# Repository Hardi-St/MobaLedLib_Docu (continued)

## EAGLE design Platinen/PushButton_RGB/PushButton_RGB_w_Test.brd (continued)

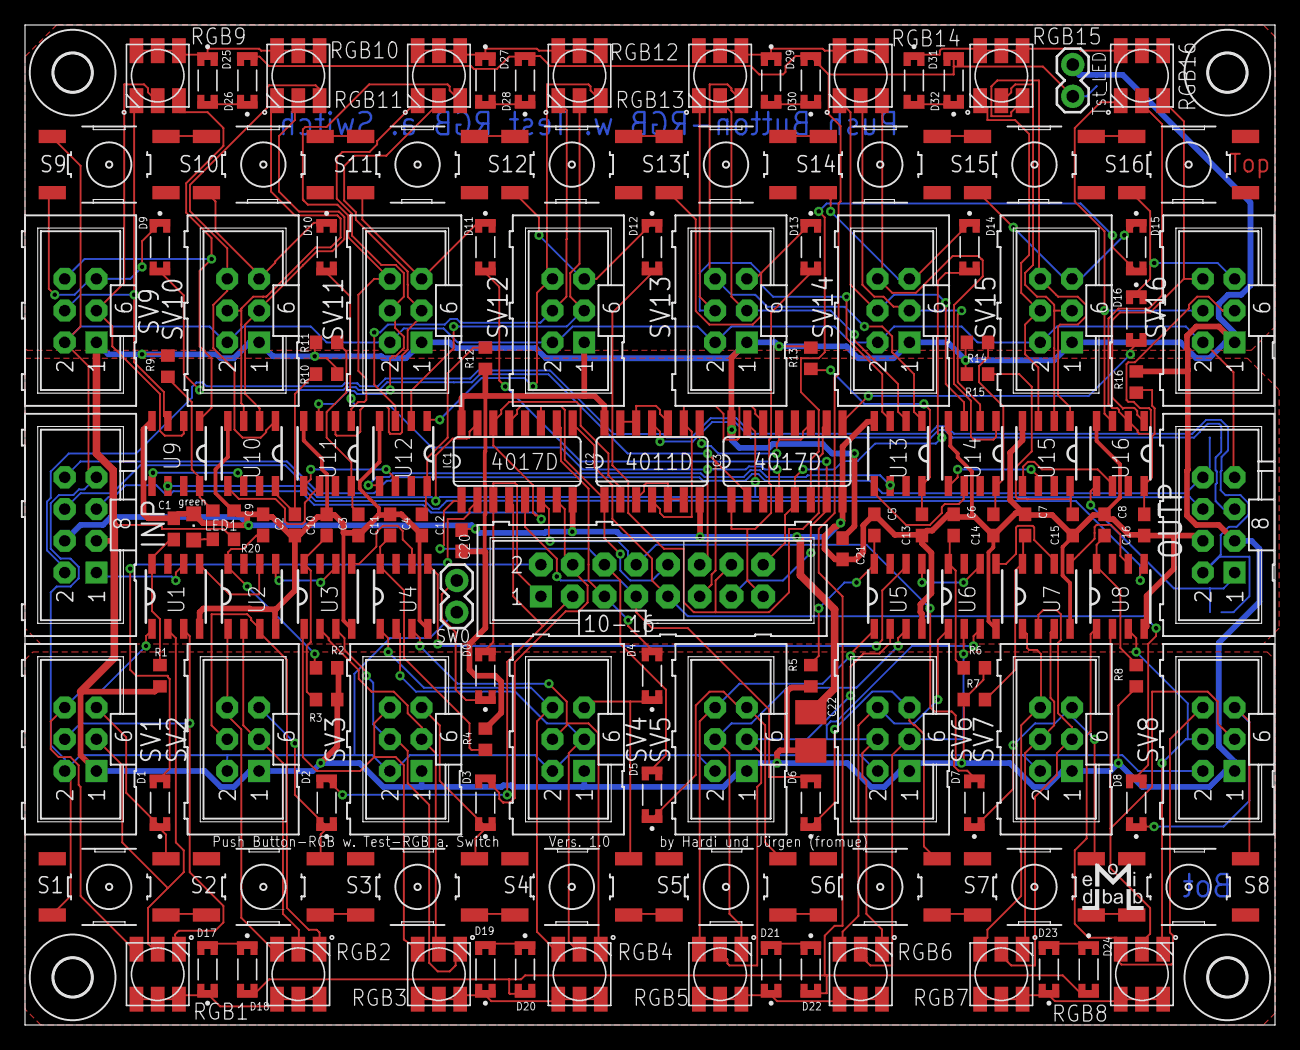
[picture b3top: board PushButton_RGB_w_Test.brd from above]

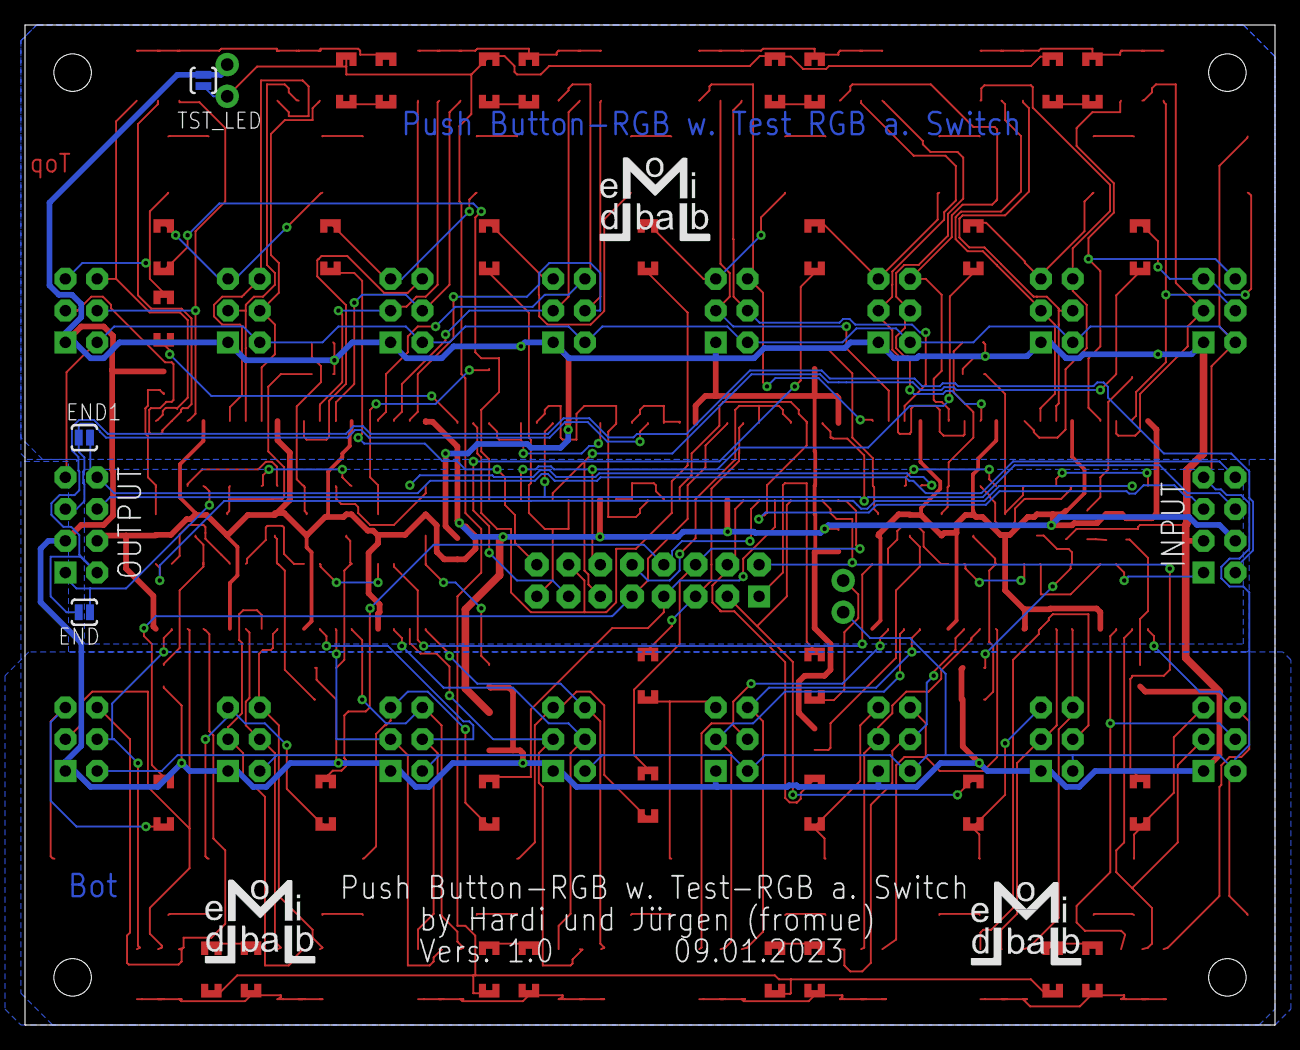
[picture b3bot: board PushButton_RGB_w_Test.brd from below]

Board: 2 copper layers, 100.0 x 80.0 mm, 149 parts (3 on the bottom side), 160 nets.

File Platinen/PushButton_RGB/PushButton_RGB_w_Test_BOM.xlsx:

Comment | Designator | Footprint | JLCPCB Part #（optional）
E OMRON SWITCH | S1, S2, S3, S4, S5, S6, S7, S8, S9, S10, S11, S12, S13, S14, S15, S16 | B3F-10XX_SMD | C83916
E WS2811 | U1, U2, U3, U4, U5, U6, U7, U8, U9, U10, U11, U12, U13, U14, U15, U16 | SOP8 | C114581
B 100nF | C1, C2, C3, C4, C5, C6, C7, C8, C9, C10, C11, C12, C13, C14, C15, C16, C20, C21 | C0603 | C14663
B 100uF CA45A-B-6.3V-100uF-K | C22 | B/3528-21R | C16133
E 4011 Quad 2-input NAND | IC2 | SO14 | C194334
E 4017 Counter | IC1, IC3 | SO16 | C356694
B 470 Ohm | R1, R2, R3, R4, R5, R6, R7, R8, R9, R10, R11, R12, R13, R14, R15, R16, R20 | R0603 | C23179
B LL4148 | D0, D1, D2, D3, D4, D5, D6, D7, D8, D9, D10, D11, D12, D13, D14, D15, D16, D17,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 | DIO_LL4148 | C9808
E 5050 RGB LED TC5050RGBF08-3CJH-AF53A | RGB1, RGB2, RGB3, RGB4, RGB5, RGB6, RGB7, RGB8, RGB9, RGB10, RGB11, RGB12, RGB1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 | RGBLED5050 | C784540

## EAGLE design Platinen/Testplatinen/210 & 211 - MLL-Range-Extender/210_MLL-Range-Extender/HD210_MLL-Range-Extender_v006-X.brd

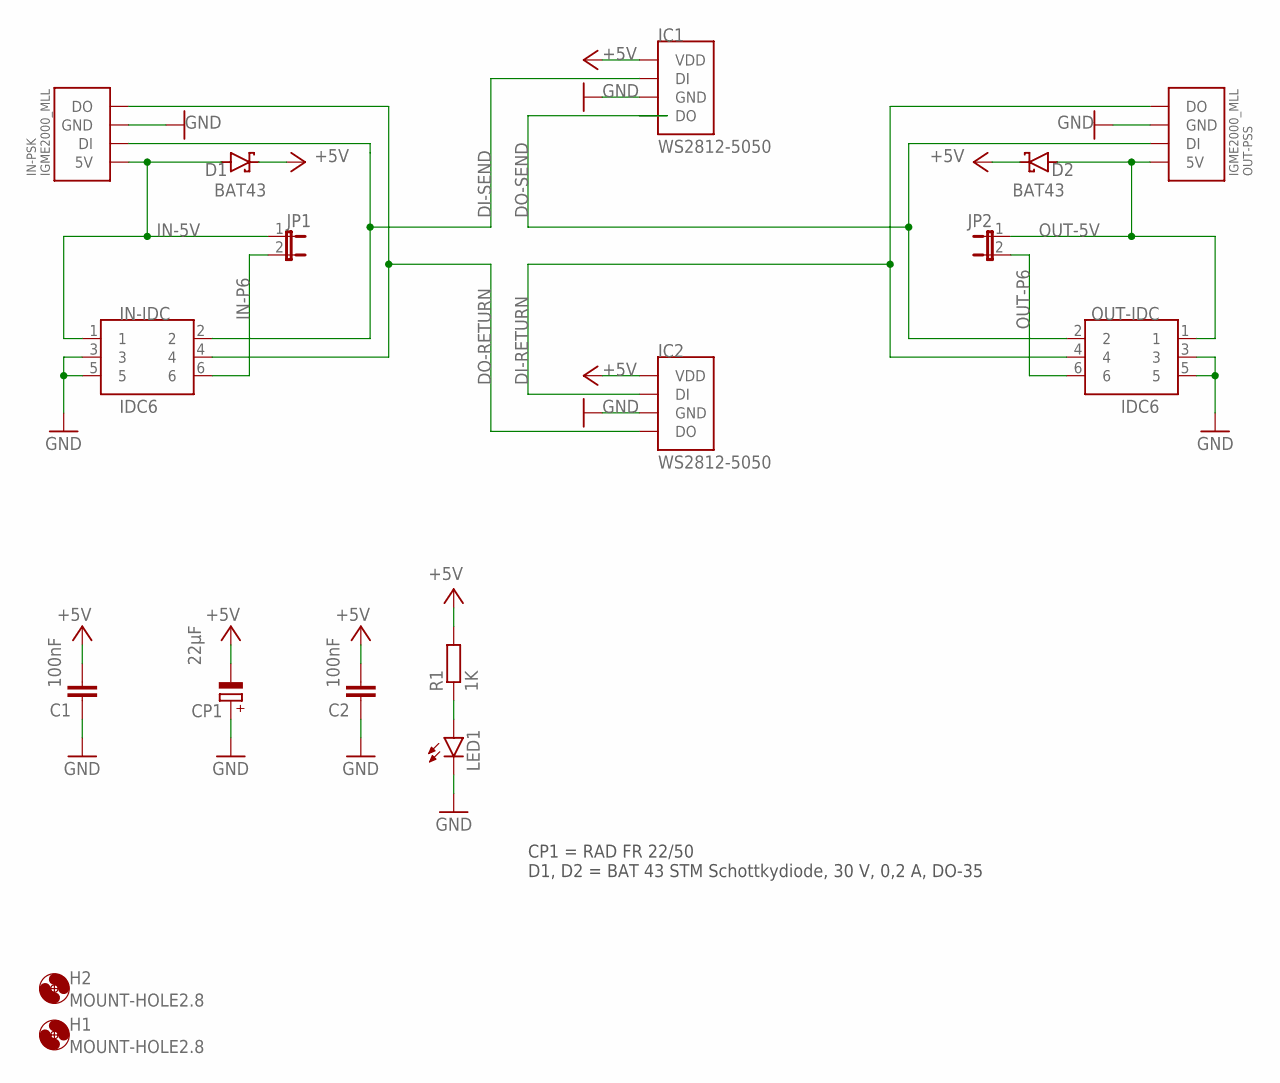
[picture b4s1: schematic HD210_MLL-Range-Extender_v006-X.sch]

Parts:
C1, C2: 100nF; C025-025X050
CP1: 22µF; E2-5
D1, D2: BAT43; DO35-10
H1, H2: MOUNT-HOLE2.8; 2,8
IC1, IC2: WS2812-5050; 5050
IN-IDC: IDC6
IN-PSK: IGME2000_MLL; PSSW4-SHORT
JP1, JP2: JP1E; JP1
LED1: LED3MM
OUT-IDC: IDC6
OUT-PSS: IGME2000_MLL; PSSW4-SHORT
R1: 1K; 0207/10

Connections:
+5V: C1.2, C2.2, CP1.-, D1.C, D2.C, IC1.VCC (VDD), IC2.VCC (VDD), R1.2
DI-RETURN: IC2.DI, OUT-IDC.4, OUT-PSS.P$1 (DO)
DI-SEND: IC1.DI, IN-IDC.2, IN-PSK.P$2 (DI)
DO-RETURN: IC2.DO, IN-IDC.4, IN-PSK.P$1 (DO)
DO-SEND: IC1.DO, OUT-IDC.2, OUT-PSS.P$2 (DI)
GND: C1.1, C2.1, CP1.+, IC1.GND, IC2.GND, IN-IDC.3, IN-IDC.5, IN-PSK.P$4 (GND), LED1.K (C), OUT-IDC.3, OUT-IDC.5, OUT-PSS.P$4 (GND)
IN-5V: D1.A, IN-IDC.1, IN-PSK.P$3 (5V), JP1.1
IN-P6: IN-IDC.6, JP1.2
unnamed: LED1.A, R1.1
OUT-5V: D2.A, JP2.1, OUT-IDC.1, OUT-PSS.P$3 (5V)
OUT-P6: JP2.2, OUT-IDC.6

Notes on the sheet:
CP1 = RAD FR 22/50 D1, D2 = BAT 43 STM Schottkydiode, 30 V, 0,2 A, DO-35

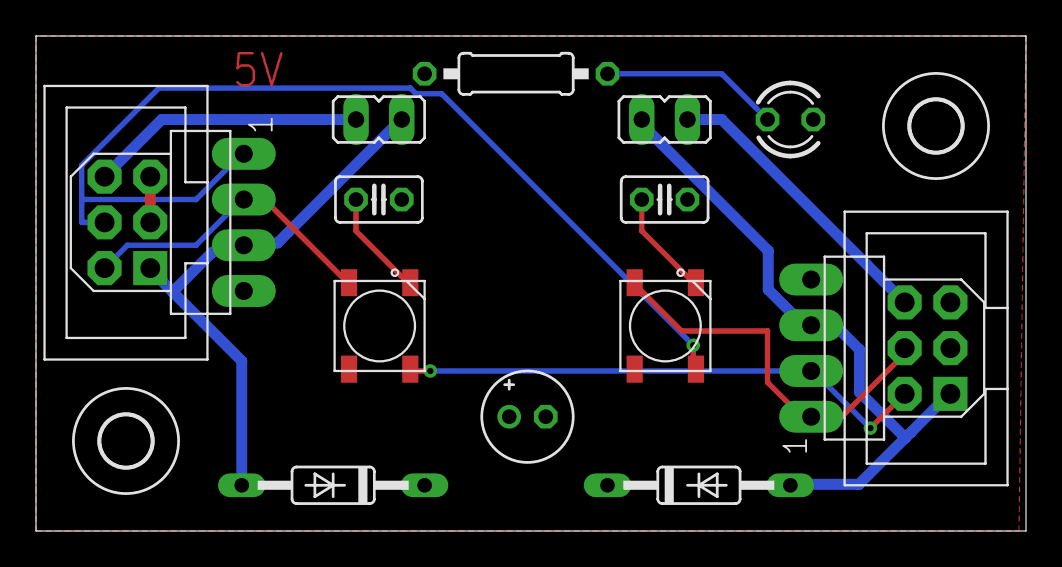
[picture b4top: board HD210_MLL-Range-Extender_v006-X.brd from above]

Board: 2 copper layers, 55.0 x 27.5 mm, 17 parts (0 on the bottom side), 11 nets.

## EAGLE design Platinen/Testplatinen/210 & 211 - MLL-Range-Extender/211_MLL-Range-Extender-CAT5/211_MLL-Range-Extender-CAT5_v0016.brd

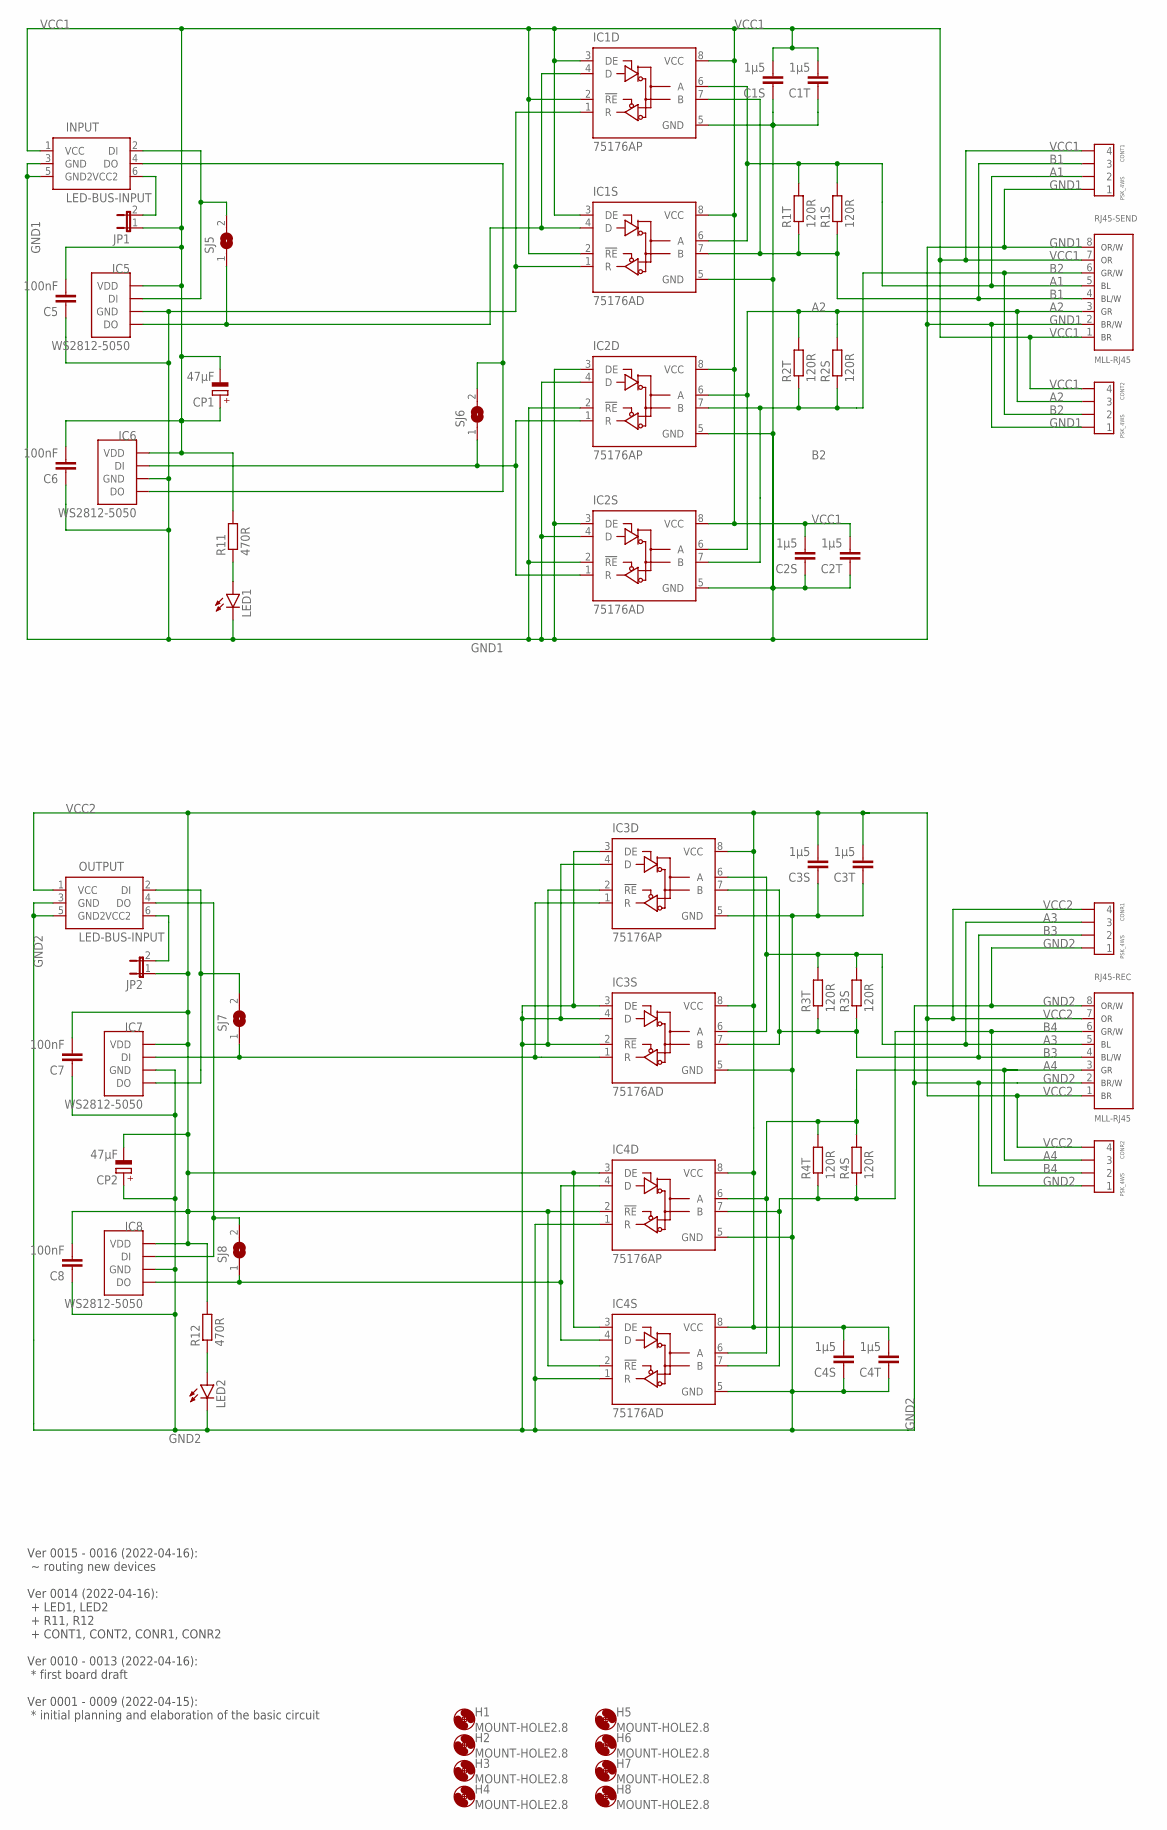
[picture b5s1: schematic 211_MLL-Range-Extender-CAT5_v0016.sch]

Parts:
C1S, C2S, C3S, C4S: 1µ5; C1210
C1T, C2T, C3T, C4T: 1µ5; C050-025X075
C5, C6, C7, C8: 100nF; C025-025X050
CONR1, CONR2: PSK_4WS; PSSW4-SHORT
CONT1, CONT2: PSK_4WS; PSSW4-SHORT
CP1, CP2: 47µF; E2-5
H1, H2, H3, H4, H5, H6, H7, H8: MOUNT-HOLE2.8; 2,8
IC1D, IC2D, IC3D, IC4D: 75176AP; DIL08
IC1S, IC2S, IC3S, IC4S: 75176AD; D_R-PDSO-G8
IC5, IC6, IC7, IC8: WS2812-5050; 5050
INPUT: LED-BUS-INPUT; IDC6
JP1, JP2: JP1E; JP1
LED1, LED2: LED3MM
OUTPUT: LED-BUS-INPUT; IDC6
R1S, R2S, R3S, R4S: 120R; R1210
R1T, R2T, R3T, R4T: 120R; 0207/10
R11, R12: 470R; 0207/10
RJ45-REC, RJ45-SEND: MLL-RJ45; RJ45_U
SJ5, SJ6, SJ7, SJ8: SJ

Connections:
A1: CONT1.P$2 (2), IC1D.6 (A), IC1S.6 (A), R1S.2, R1T.2, RJ45-SEND.5 (BLUE)
A2: CONT2.P$3 (3), IC2D.6 (A), IC2S.6 (A), R2S.2, R2T.2, RJ45-SEND.3 (GREEN)
A3: CONR1.P$3 (3), IC3D.6 (A), IC3S.6 (A), R3S.2, R3T.2, RJ45-REC.5 (BLUE)
A4: CONR2.P$3 (3), IC4D.6 (A), IC4S.6 (A), R4S.2, R4T.2, RJ45-REC.3 (GREEN)
B1: CONT1.P$3 (3), IC1D.7 (B), IC1S.7 (B), R1S.1, R1T.1, RJ45-SEND.4 (BLUE/WHITE)
B2: CONT2.P$2 (2), IC2D.7 (B), IC2S.7 (B), R2S.1, R2T.1, RJ45-SEND.6 (GREEN/WHITE)
B3: CONR1.P$2 (2), IC3D.7 (B), IC3S.7 (B), R3S.1, R3T.1, RJ45-REC.4 (BLUE/WHITE)
B4: CONR2.P$2 (2), IC4D.7 (B), IC4S.7 (B), R4S.1, R4T.1, RJ45-REC.6 (GREEN/WHITE)
GND1: C1S.1, C1T.1, C2S.1, C2T.1, C5.1, C6.1, CONT1.P$1 (1), CONT2.P$1 (1), IC1D.1 (R), IC1D.5 (GND), IC1S.1 (R), IC1S.5 (GND), IC2D.2 (!RE), IC2D.3 (DE), IC2D.4 (D), IC2D.5 (GND), IC2S.2 (!RE), IC2S.3 (DE), IC2S.4 (D), IC2S.5 (GND), IC5.GND, IC6.GND, INPUT.3 (GND), INPUT.5 (GND2), LED1.K (C), RJ45-SEND.2 (BROWN/WHITE), RJ45-SEND.8 (ORANGE/WHITE)
GND2: C3S.1, C3T.1, C4S.1, C4T.1, C7.1, C8.1, CONR1.P$1 (1), CONR2.P$1 (1), CP2.+, IC3D.2 (!RE), IC3D.3 (DE), IC3D.4 (D), IC3D.5 (GND), IC3S.2 (!RE), IC3S.3 (DE), IC3S.4 (D), IC3S.5 (GND), IC4D.1 (R), IC4D.5 (GND), IC4S.1 (R), IC4S.5 (GND), IC7.GND, IC8.GND, LED2.K (C), OUTPUT.3 (GND), OUTPUT.5 (GND2), RJ45-REC.2 (BROWN/WHITE), RJ45-REC.8 (ORANGE/WHITE)
unnamed: JP2.2, OUTPUT.6 (VCC2)
unnamed: INPUT.6 (VCC2), JP1.2
unnamed: IC1D.4 (D), IC1S.4 (D), IC5.DO, SJ5.1
unnamed: LED1.A, R11.1
unnamed: IC7.DO, OUTPUT.2 (DI), SJ7.2
unnamed: IC8.DI, OUTPUT.4 (DO), SJ8.2
unnamed: LED2.A, R12.1
unnamed: IC2D.1 (R), IC2S.1 (R), IC6.DI, SJ6.1
unnamed: IC5.DI, INPUT.2 (DI), SJ5.2
unnamed: IC6.DO, INPUT.4 (DO), SJ6.2
unnamed: IC3D.1 (R), IC3S.1 (R), IC7.DI, SJ7.1
unnamed: IC4D.4 (D), IC4S.4 (D), IC8.DO, SJ8.1
VCC1: C1S.2, C1T.2, C2S.2, C2T.2, C5.2, C6.2, CONT1.P$4 (4), CONT2.P$4 (4), CP1.+, CP1.-, IC1D.2 (!RE), IC1D.3 (DE), IC1D.8 (VCC), IC1S.2 (!RE), IC1S.3 (DE), IC1S.8 (VCC), IC2D.8 (VCC), IC2S.8 (VCC), IC5.VCC (VDD), IC6.VCC (VDD), INPUT.1 (VCC), JP1.1, R11.2, RJ45-SEND.1 (BROWN), RJ45-SEND.7 (OPRANGE)
VCC2: C3S.2, C3T.2, C4S.2, C4T.2, C7.2, C8.2, CONR1.P$4 (4), CONR2.P$4 (4), CP2.-, IC3D.8 (VCC), IC3S.8 (VCC), IC4D.2 (!RE), IC4D.3 (DE), IC4D.8 (VCC), IC4S.2 (!RE), IC4S.3 (DE), IC4S.8 (VCC), IC7.VCC (VDD), IC8.VCC (VDD), JP2.1, OUTPUT.1 (VCC), R12.2, RJ45-REC.1 (BROWN), RJ45-REC.7 (OPRANGE)

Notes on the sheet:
Ver 0015 - 0016 (2022-04-16): ~ routing new devices Ver 0014 (2022-04-16): + LED1, LED2 + R11, R12 + CONT1, CONT2, CONR1, CONR2 Ver 0010 - 0013 (2022-04-16): * first board draft Ver 0001 - 0009 (2022-04-15): * initial planning and elaboration of the basic circuit

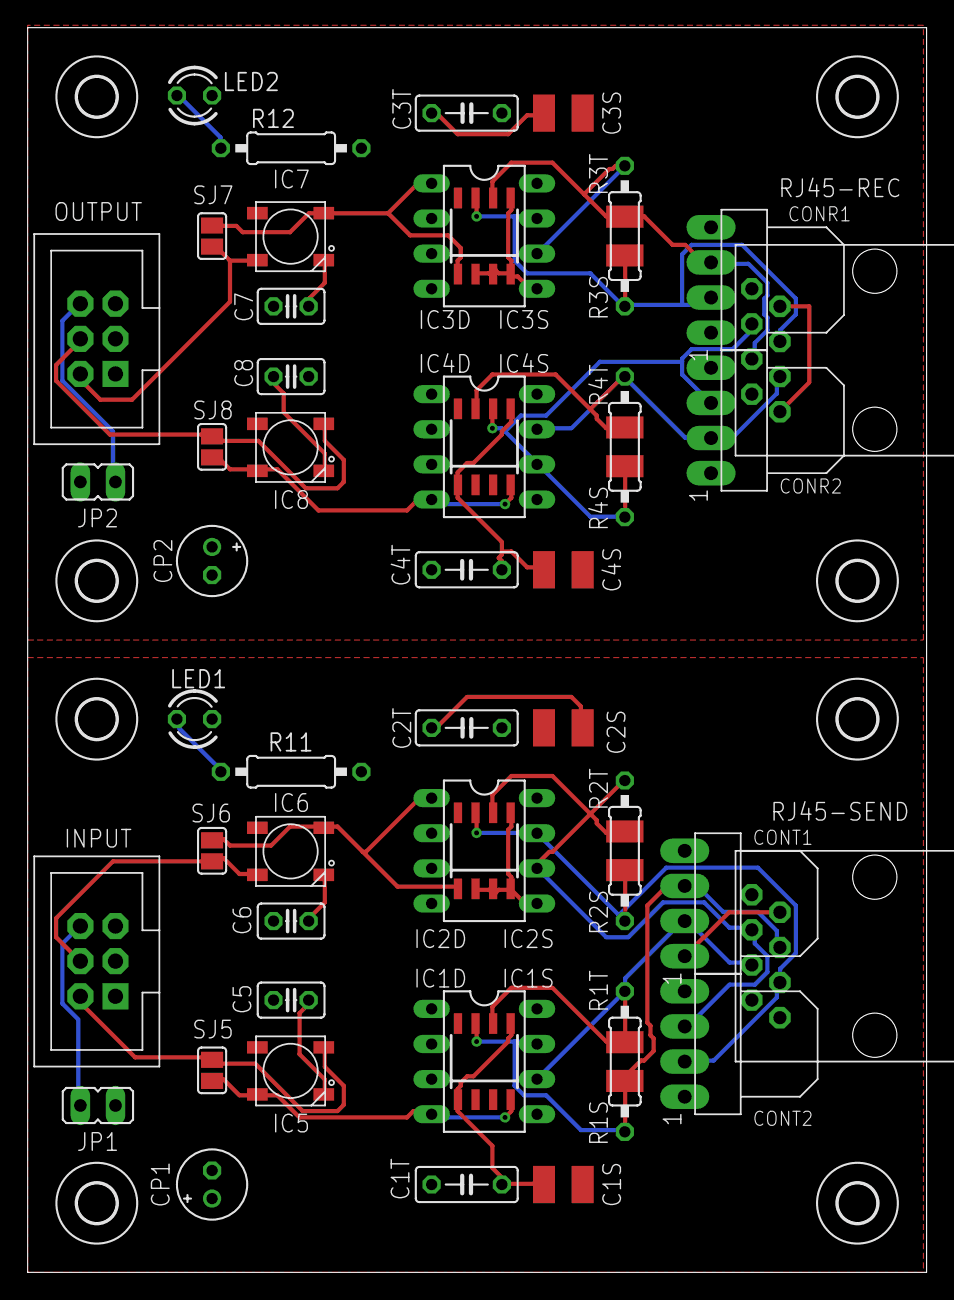
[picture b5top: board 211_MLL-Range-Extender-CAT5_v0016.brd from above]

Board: 2 copper layers, 65.0 x 90.0 mm, 60 parts (0 on the bottom side), 24 nets.

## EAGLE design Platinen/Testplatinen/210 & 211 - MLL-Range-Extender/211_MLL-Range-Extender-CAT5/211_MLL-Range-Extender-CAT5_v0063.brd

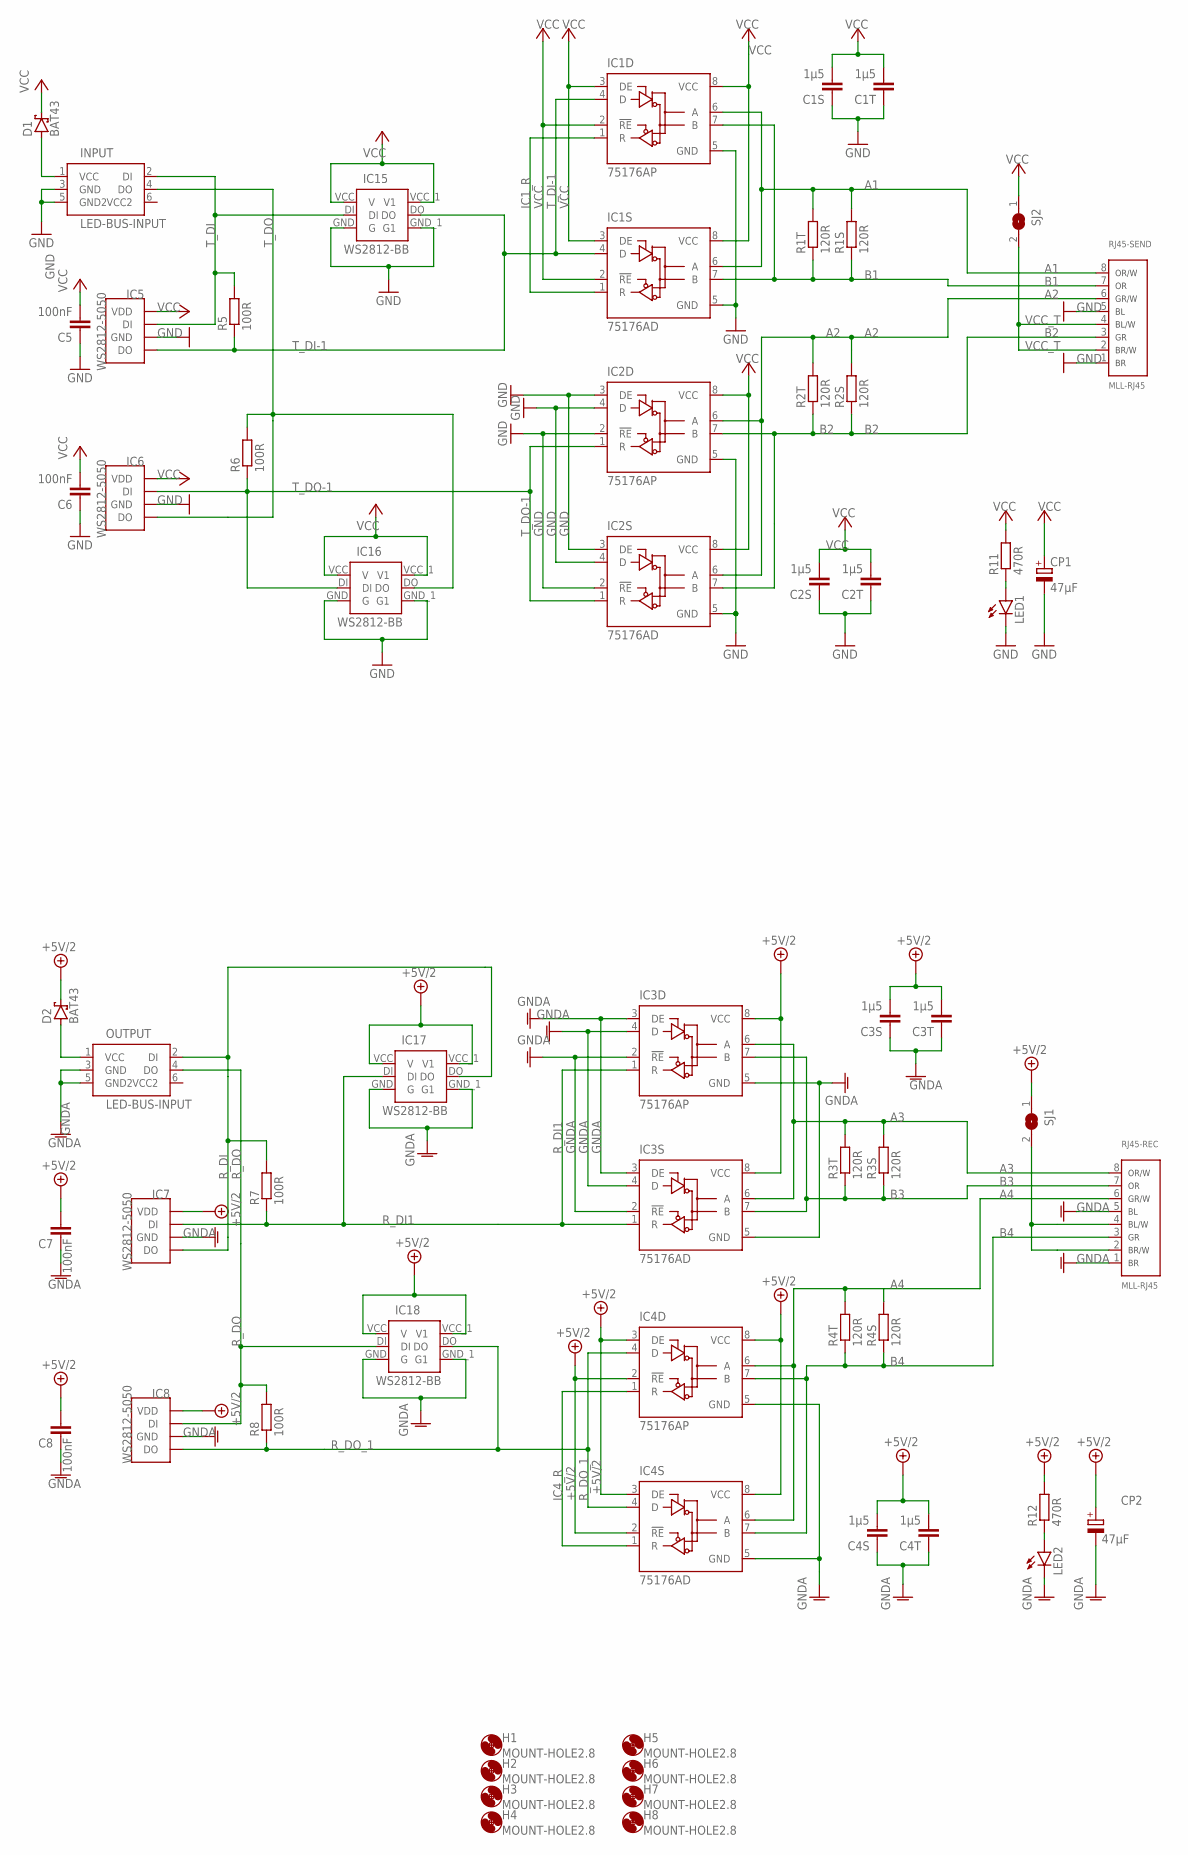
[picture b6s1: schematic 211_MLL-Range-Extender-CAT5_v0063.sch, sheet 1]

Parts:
C1S, C2S, C3S, C4S: 1µ5; C1210
C1T, C2T, C3T, C4T: 1µ5; C050-025X075
C5, C6, C7, C8: 100nF; C025-025X050
CP1, CP2: 47µF; E2-5
D1, D2: BAT43; DO35-10
H1, H2, H3, H4, H5, H6, H7, H8: MOUNT-HOLE2.8; 2,8
IC1D, IC2D, IC3D, IC4D: 75176AP; DIL08
IC1S, IC2S, IC3S, IC4S: 75176AD; D_R-PDSO-G8
IC5, IC6, IC7, IC8: WS2812-5050; 5050
IC15, IC16, IC17, IC18: WS2812-BB; WS2812B-PCB2
INPUT: LED-BUS-INPUT; IDC6
LED1, LED2: LED3MM
OUTPUT: LED-BUS-INPUT; IDC6
R1S, R2S, R3S, R4S: 120R; R1210
R1T, R2T, R3T, R4T: 120R; 0207/10
R5, R6, R7, R8: 100R; 0207/10
R11, R12: 470R; 0207/10
RJ45-REC, RJ45-SEND: MLL-RJ45; RJ45_U
SJ1, SJ2: SJ

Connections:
+5V/2: C3S.2, C3T.2, C4S.2, C4T.2, C7.2, C8.2, CP2.+, D2.C, IC3D.8 (VCC), IC3S.8 (VCC), IC4D.2 (!RE), IC4D.3 (DE), IC4D.8 (VCC), IC4S.2 (!RE), IC4S.3 (DE), IC4S.8 (VCC), IC7.VCC (VDD), IC8.VCC (VDD), IC17.VCC (V), IC17.VCC_1 (V1), IC18.VCC (V), IC18.VCC_1 (V1), R12.2, SJ1.1
A1: IC1D.6 (A), IC1S.6 (A), R1S.2, R1T.2, RJ45-SEND.8 (ORANGE/WHITE)
A2: IC2D.6 (A), IC2S.6 (A), R2S.2, R2T.2, RJ45-SEND.6 (GREEN/WHITE)
A3: IC3D.6 (A), IC3S.6 (A), R3S.2, R3T.2, RJ45-REC.8 (ORANGE/WHITE)
A4: IC4D.6 (A), IC4S.6 (A), R4S.2, R4T.2, RJ45-REC.6 (GREEN/WHITE)
B1: IC1D.7 (B), IC1S.7 (B), R1S.1, R1T.1, RJ45-SEND.7 (OPRANGE)
B2: IC2D.7 (B), IC2S.7 (B), R2S.1, R2T.1, RJ45-SEND.3 (GREEN)
B3: IC3D.7 (B), IC3S.7 (B), R3S.1, R3T.1, RJ45-REC.7 (OPRANGE)
B4: IC4D.7 (B), IC4S.7 (B), R4S.1, R4T.1, RJ45-REC.3 (GREEN)
GND: C1S.1, C1T.1, C2S.1, C2T.1, C5.1, C6.1, CP1.-, IC1D.5 (GND), IC1S.5 (GND), IC2D.2 (!RE), IC2D.3 (DE), IC2D.4 (D), IC2D.5 (GND), IC2S.2 (!RE), IC2S.3 (DE), IC2S.4 (D), IC2S.5 (GND), IC5.GND, IC6.GND, IC15.GND (G), IC15.GND_1 (G1), IC16.GND (G), IC16.GND_1 (G1), INPUT.3 (GND), INPUT.5 (GND2), LED1.K (C), RJ45-SEND.1 (BROWN), RJ45-SEND.5 (BLUE)
GNDA: C3S.1, C3T.1, C4S.1, C4T.1, C7.1, C8.1, CP2.-, IC3D.2 (!RE), IC3D.3 (DE), IC3D.4 (D), IC3D.5 (GND), IC3S.2 (!RE), IC3S.3 (DE), IC3S.4 (D), IC3S.5 (GND), IC4D.5 (GND), IC4S.5 (GND), IC7.GND, IC8.GND, IC17.GND (G), IC17.GND_1 (G1), IC18.GND (G), IC18.GND_1 (G1), LED2.K (C), OUTPUT.3 (GND), OUTPUT.5 (GND2), RJ45-REC.1 (BROWN), RJ45-REC.5 (BLUE)
IC1_R: IC1D.1 (R), IC1S.1 (R)
IC4_R: IC4D.1 (R), IC4S.1 (R)
LED1-R: LED1.A, R11.1
LED2_R: LED2.A, R12.1
unnamed: D1.A, INPUT.1 (VCC)
R_DI: IC7.DO, IC17.DO, OUTPUT.2 (DI), R7.2
R_DI1: IC3D.1 (R), IC3S.1 (R), IC7.DI, IC17.DI, R7.1
R_DO: IC8.DI, IC18.DI, OUTPUT.4 (DO), R8.2
R_DO_1: IC4D.4 (D), IC4S.4 (D), IC8.DO, IC18.DO, R8.1
T_DI: IC5.DI, IC15.DI, INPUT.2 (DI), R5.2
T_DI-1: IC1D.4 (D), IC1S.4 (D), IC5.DO, IC15.DO, R5.1
T_DO: IC6.DO, IC16.DO, INPUT.4 (DO), R6.2
T_DO-1: IC2D.1 (R), IC2S.1 (R), IC6.DI, IC16.DI, R6.1
VCC: C1S.2, C1T.2, C2S.2, C2T.2, C5.2, C6.2, CP1.+, D1.C, IC1D.2 (!RE), IC1D.3 (DE), IC1D.8 (VCC), IC1S.2 (!RE), IC1S.3 (DE), IC1S.8 (VCC), IC2D.8 (VCC), IC2S.8 (VCC), IC5.VCC (VDD), IC6.VCC (VDD), IC15.VCC (V), IC15.VCC_1 (V1), IC16.VCC (V), IC16.VCC_1 (V1), R11.2, SJ2.1
VCC2: INPUT.6 (VCC2)
VCC_T: RJ45-SEND.2 (BROWN/WHITE), RJ45-SEND.4 (BLUE/WHITE), SJ2.2
VDD: OUTPUT.6 (VCC2)
VDD_IN: D2.A, OUTPUT.1 (VCC)
VDD_T: RJ45-REC.2 (BROWN/WHITE), RJ45-REC.4 (BLUE/WHITE), SJ1.2

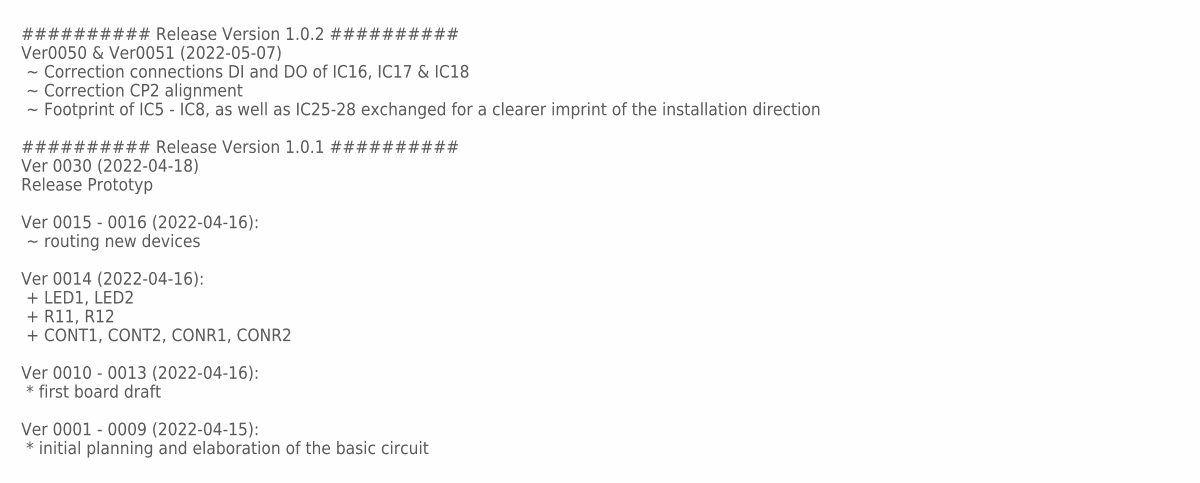
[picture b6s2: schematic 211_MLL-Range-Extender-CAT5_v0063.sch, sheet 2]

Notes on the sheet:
########## Release Version 1.0.2 ########## Ver0050 & Ver0051 (2022-05-07) ~ Correction connections DI and DO of IC16, IC17 & IC18 ~ Correction CP2 alignment ~ Footprint of IC5 - IC8, as well as IC25-28 exchanged for a clearer imprint of the installation direction ########## Release Version 1.0.1 #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

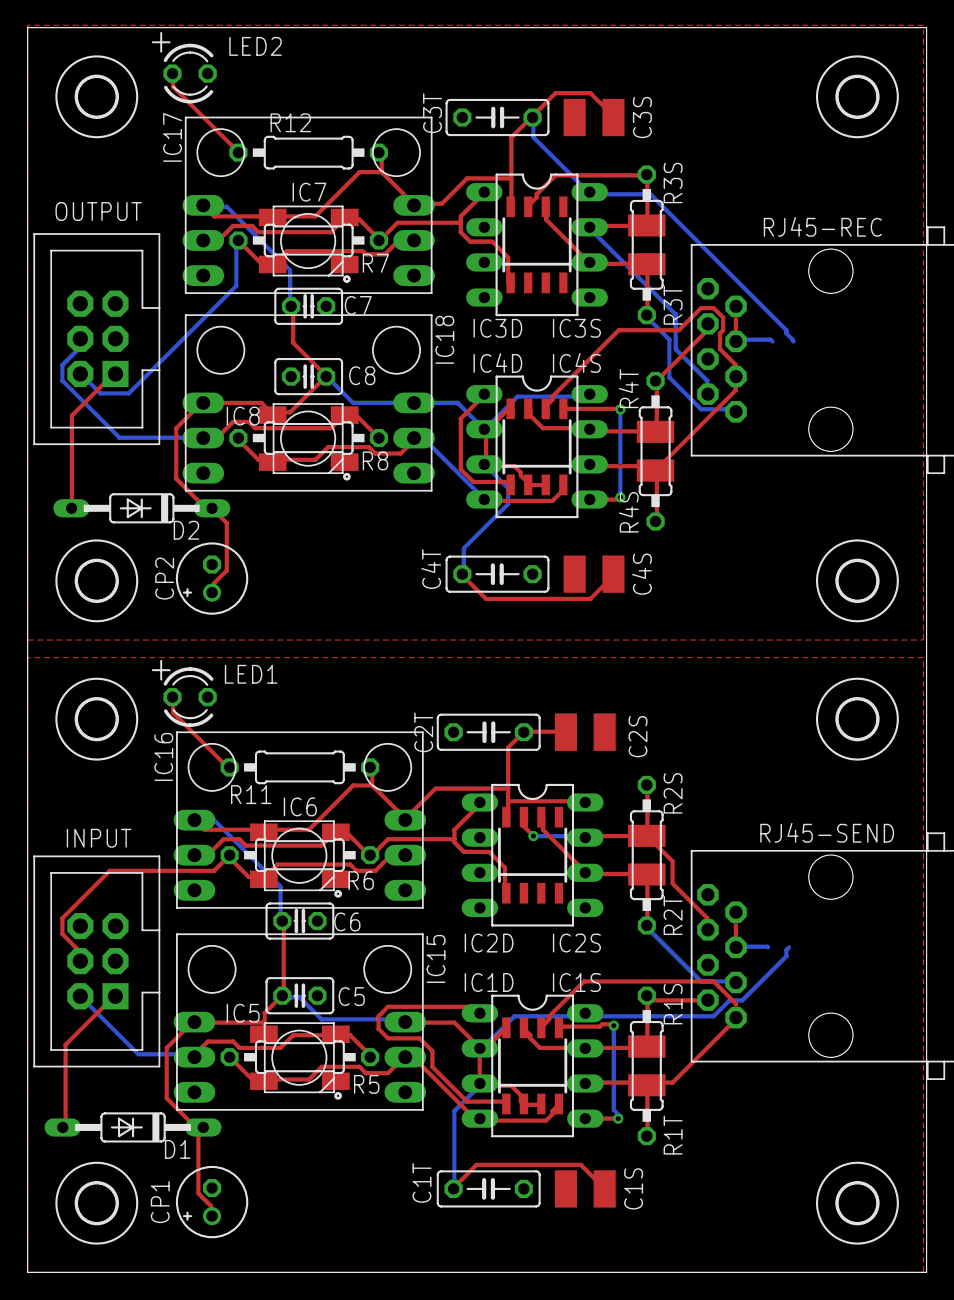
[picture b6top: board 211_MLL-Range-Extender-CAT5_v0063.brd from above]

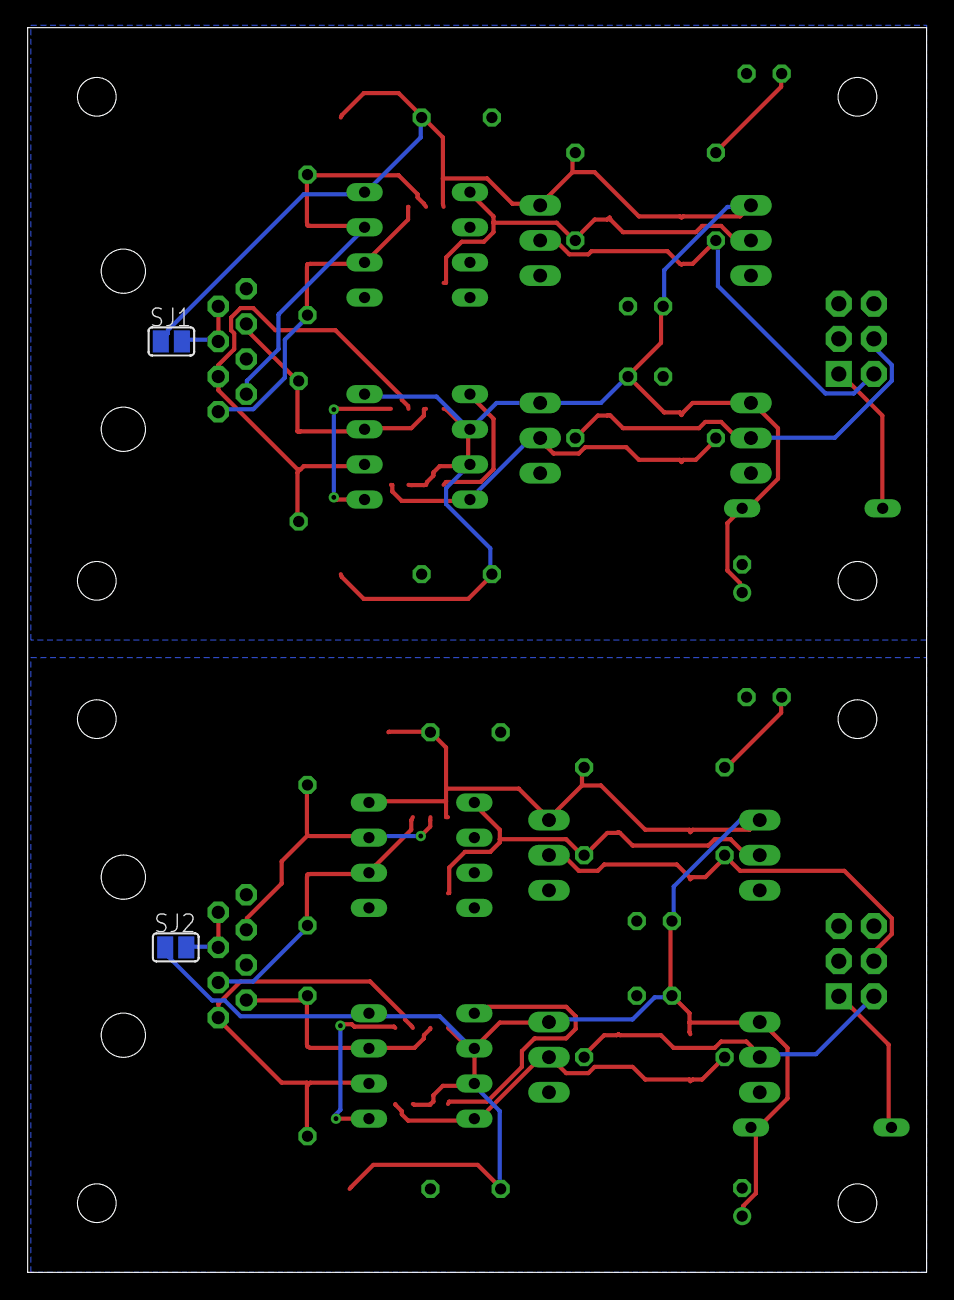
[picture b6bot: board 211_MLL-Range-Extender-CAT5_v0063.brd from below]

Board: 2 copper layers, 65.0 x 90.0 mm, 62 parts (2 on the bottom side), 28 nets.

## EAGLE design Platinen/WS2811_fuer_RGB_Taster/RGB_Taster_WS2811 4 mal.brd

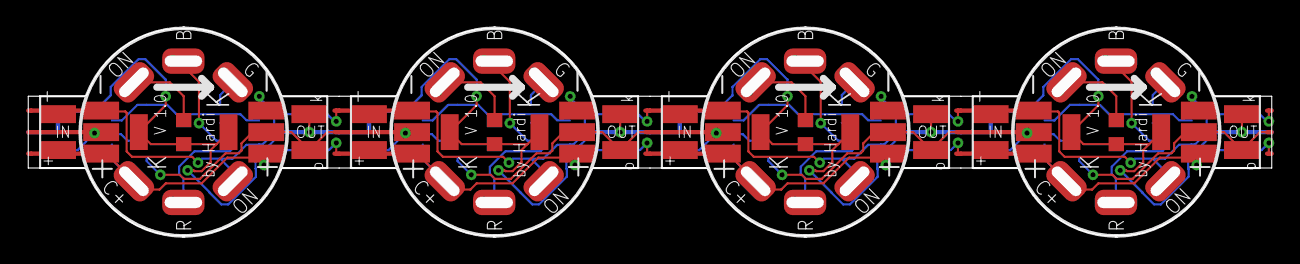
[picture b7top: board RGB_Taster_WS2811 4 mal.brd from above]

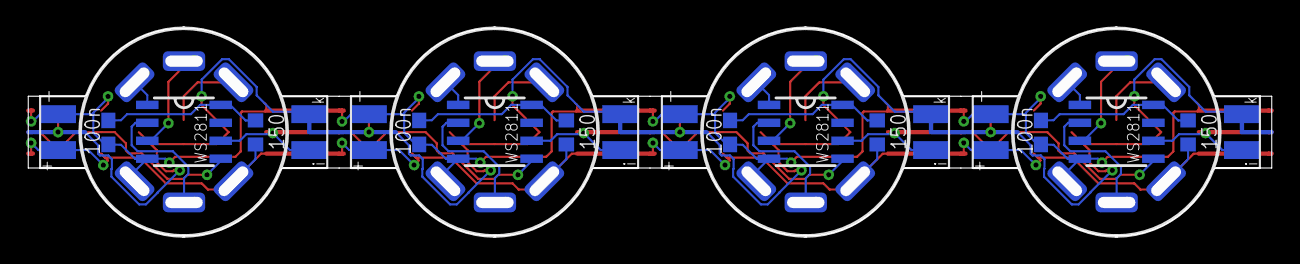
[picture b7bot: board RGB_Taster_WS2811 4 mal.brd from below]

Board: 2 copper layers, 88.0 x 14.7 mm, 104 parts (28 on the bottom side), 28 nets.

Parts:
B, B1, B2, B3: LANG_LOCH2
C1, C2, C3, C4: 100n; C0603
C+, C+1, C+2, C+3: LANG_LOCH2
G, G1, G2, G3: LANG_LOCH2
ON1, ON2, ON3, ON4, ON5, ON6, ON7, ON8: LANG_LOCH2
PI1, PI2, PI3, PI4, PI5, PI6, PI7, PI8, PI9, PI10, PI11, PI12, PI13, PI14, PI15, PI16: SMD1,27-2,54
PO1, PO2, PO3, PO4, PO5, PO6, PO7, PO8, PO9, PO10, PO11, PO12, PO13, PO14, PO15, PO16: SMD1,27-2,54
R, R3, R6, R9: LANG_LOCH2
R1, R4, R7, R10: 150; RCL_R0603
R2, R5, R8, R11: ?; RCL_R0603
SI1, SI2, SI3, SI4, SI5, SI6, SI7, SI8, SI9, SI10, SI11, SI12, SI13, SI14, SI15, SI16: SMD1,27-2,54
SO1, SO2, SO3, SO4, SO5, SO6, SO7, SO8, SO9, SO10, SO11, SO12, SO13, SO14, SO15, SO16: SMD1,27-2,54
U1, U2, U3, U4: WS2811; SOP8

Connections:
+5V: C+.P$1, C+.P$2, C+1.P$1, C+1.P$2, C+2.P$1, C+2.P$2, C+3.P$1, C+3.P$2, PI1.1, PI6.1, PI10.1, PI14.1, PO1.1, PO6.1, PO10.1, PO14.1, R1.1, R4.1, R7.1, R10.1, SI1.1, SI5.1, SI9.1, SI13.1, SO1.1, SO6.1, SO10.1, SO14.1
BUT: PI4.1, PI8.1, PI12.1, PI16.1, PO4.1, PO8.1, PO12.1, PO16.1, R2.1, R5.1, R8.1, R11.1, SI4.1, SI8.1, SI12.1, SI16.1, SO4.1, SO8.1, SO12.1, SO16.1
DIN: PI2.1, SI2.1, U3.6
DIN1: PI5.1, PO2.1, SI6.1, SO2.1, U1.6, U3.5
DIN2: PI9.1, PO5.1, SI10.1, SO5.1, U1.5, U2.6
DIN3: PI13.1, PO9.1, SI14.1, SO9.1, U2.5, U4.6
DOUT3: PO13.1, SO13.1, U4.5
GND: C1.2, C2.2, C3.2, C4.2, ON2.P$1, ON2.P$2, ON4.P$1, ON4.P$2, ON6.P$1, ON6.P$2, ON8.P$1, ON8.P$2, PI3.1, PI7.1, PI11.1, PI15.1, PO3.1, PO7.1, PO11.1, PO15.1, SI3.1, SI7.1, SI11.1, SI15.1, SO3.1, SO7.1, SO11.1, SO15.1, U1.4, U2.4, U3.4, U4.4
unnamed: C2.1, R4.2, U1.8
unnamed: B.P$1, B.P$2, U3.3
unnamed: R.P$1, R.P$2, U3.2
unnamed: C1.1, R1.2, U3.8
unnamed: G.P$1, G.P$2, U3.1
unnamed: ON1.P$1, ON1.P$2, R2.2
unnamed: B1.P$1, B1.P$2, U1.3
unnamed: R3.P$1, R3.P$2, U1.2
unnamed: G1.P$1, G1.P$2, U1.1
unnamed: ON3.P$1, ON3.P$2, R5.2
unnamed: C3.1, R7.2, U2.8
unnamed: B2.P$1, B2.P$2, U2.3
unnamed: R6.P$1, R6.P$2, U2.2
unnamed: G2.P$1, G2.P$2, U2.1
unnamed: ON5.P$1, ON5.P$2, R8.2
unnamed: C4.1, R10.2, U4.8
unnamed: B3.P$1, B3.P$2, U4.3
unnamed: R9.P$1, R9.P$2, U4.2
unnamed: G3.P$1, G3.P$2, U4.1
unnamed: ON7.P$1, ON7.P$2, R11.2
